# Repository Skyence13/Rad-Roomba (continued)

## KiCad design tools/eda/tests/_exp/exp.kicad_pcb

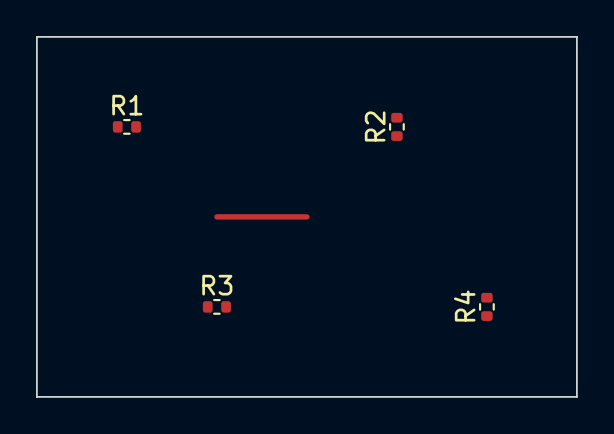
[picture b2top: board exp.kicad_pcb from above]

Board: 4 copper layers, 30.0 x 20.0 mm, 4 parts (0 on the bottom side), 2 nets.

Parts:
R1, R2, R3, R4: 10k; R_0402_1005Metric

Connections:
GND: R1.1, R2.1, R3.1, R4.1
SIG: R1.2, R2.2, R3.2, R4.2

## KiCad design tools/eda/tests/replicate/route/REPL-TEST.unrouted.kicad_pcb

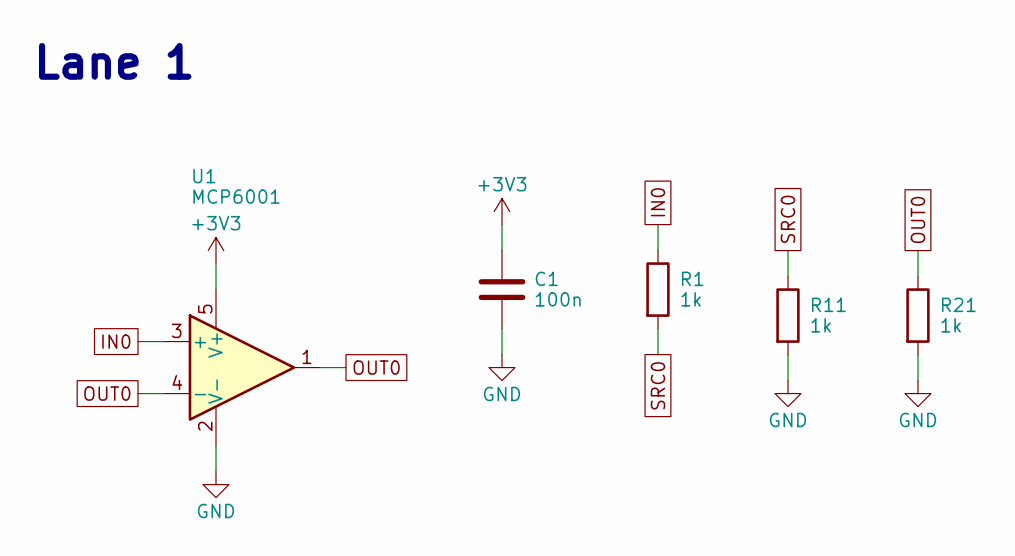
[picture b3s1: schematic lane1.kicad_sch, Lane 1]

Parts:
C1: 100n; C_0402_1005Metric; MPN GRM155R71C104KA88D
R1, R11, R21: 1k; R_0402_1005Metric; MPN RC0402FR-071KL
U1: MCP6001; SOT-23-5; MPN MCP6001T-I/OT

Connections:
+3V3: C1.1, U1.5 (V+); also elsewhere on the board
GND: C1.2, R11.2, R21.2, U1.2 (V-); also elsewhere on the board
IN0: R1.1, U1.3 (+)
OUT0: R21.1, U1.1, U1.4 (-)
SRC0: R1.2, R11.1

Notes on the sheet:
Lane 1

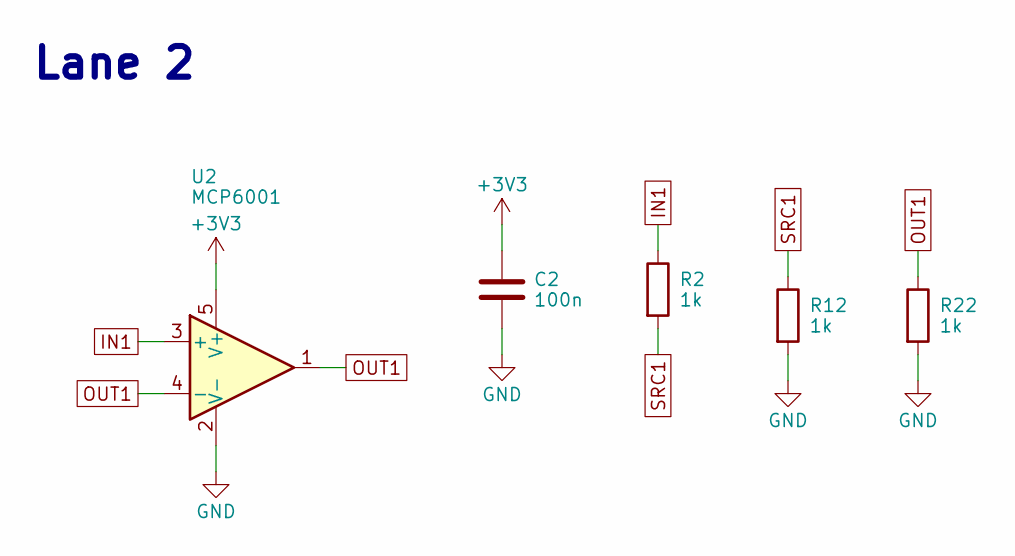
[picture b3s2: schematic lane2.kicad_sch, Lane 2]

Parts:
C2: 100n; C_0402_1005Metric; MPN GRM155R71C104KA88D
R2, R12, R22: 1k; R_0402_1005Metric; MPN RC0402FR-071KL
U2: MCP6001; SOT-23-5; MPN MCP6001T-I/OT

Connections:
+3V3: C2.1, U2.5 (V+); also elsewhere on the board
GND: C2.2, R12.2, R22.2, U2.2 (V-); also elsewhere on the board
IN1: R2.1, U2.3 (+)
OUT1: R22.1, U2.1, U2.4 (-)
SRC1: R2.2, R12.1

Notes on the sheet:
Lane 2

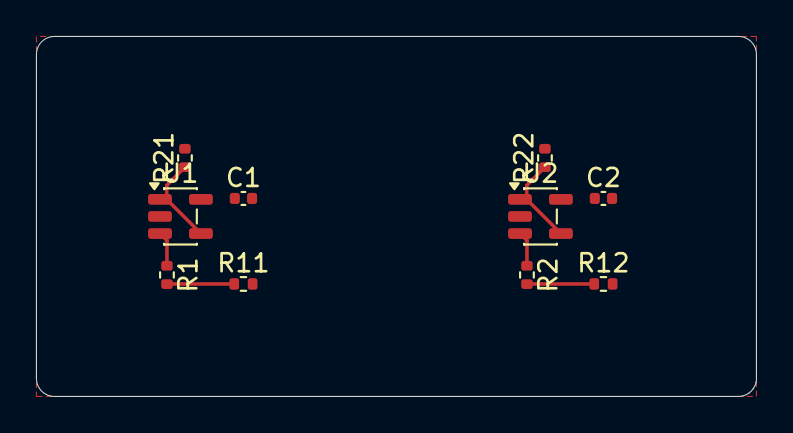
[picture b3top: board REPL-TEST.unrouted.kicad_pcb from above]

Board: 2 copper layers, 40.0 x 20.0 mm, 10 parts (0 on the bottom side), 8 nets.
